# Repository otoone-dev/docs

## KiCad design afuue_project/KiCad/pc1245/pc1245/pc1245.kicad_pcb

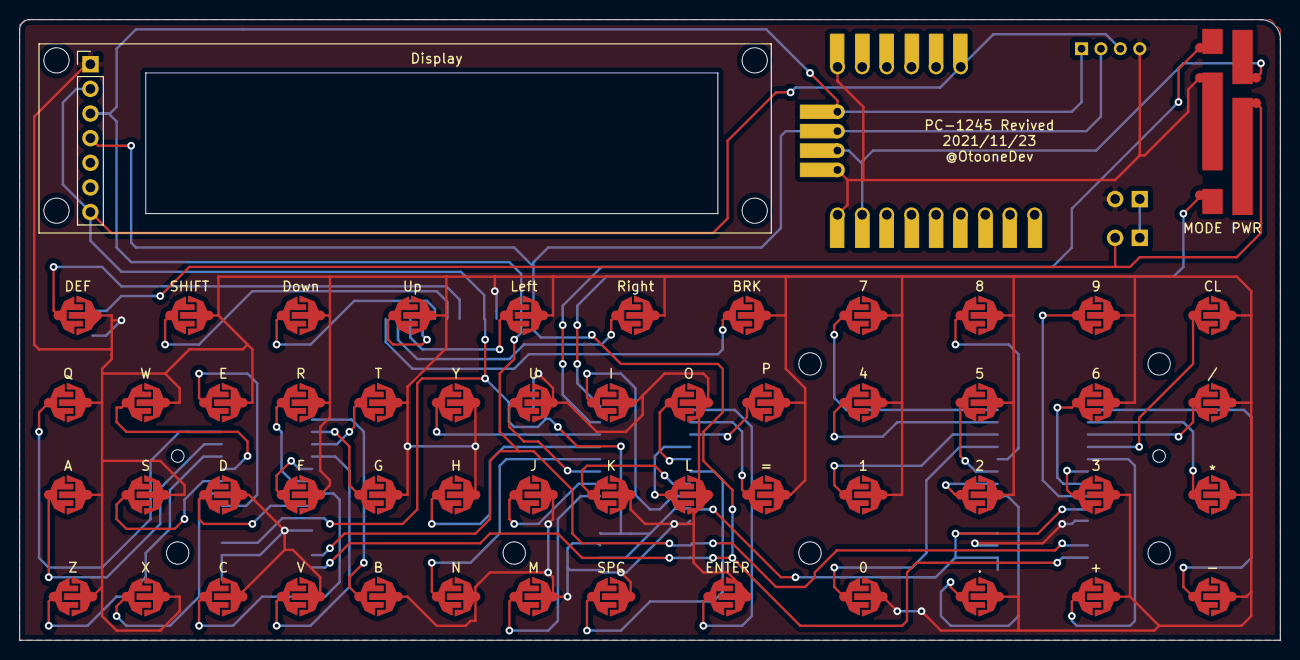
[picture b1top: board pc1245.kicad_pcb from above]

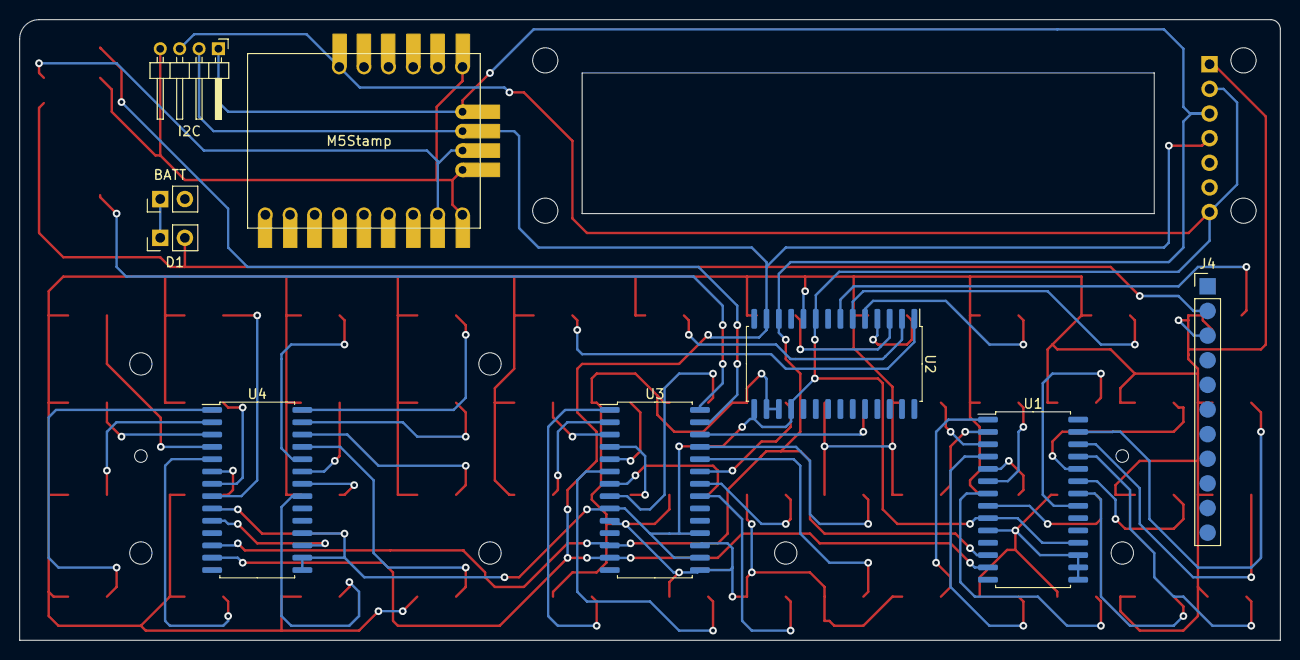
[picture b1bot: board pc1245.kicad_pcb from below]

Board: 2 copper layers, 130.0 x 64.0 mm, 64 parts (9 on the bottom side), 61 nets.

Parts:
0, 1, 2, 3, 4, 5, 6, 7, 8, 9, .: SW_Push; ContactPad_4mm
*: SW_Push; ContactPad_4mm
+: SW_Push; ContactPad_4mm
-: SW_Push; ContactPad_4mm
/: SW_Push; ContactPad_4mm
=: SW_Push; ContactPad_4mm
A: SW_Push; ContactPad_4mm
B: SW_Push; ContactPad_4mm
BATT: Conn_01x02; PinHeader_1x02_P2.54mm_Vertical
BRK: SW_Push; ContactPad_4mm
C: SW_Push; ContactPad_4mm
CL: SW_Push; ContactPad_4mm
D: SW_Push; ContactPad_4mm
D1: DIODE; PinHeader_1x02_P2.54mm_Vertical
DEF: SW_Push; ContactPad_4mm
Display: Conn_01x07; PinHeader_1x07_P2.54mm_Vertical
Down: SW_Push; ContactPad_4mm
E: SW_Push; ContactPad_4mm
ENTER: SW_Push; ContactPad_4mm
F: SW_Push; ContactPad_4mm
G: SW_Push; ContactPad_4mm
H: SW_Push; ContactPad_4mm
I: SW_Push; ContactPad_4mm
I2C: Conn_01x04; PinHeader_1x04_P2.00mm_Horizontal
J: SW_Push; ContactPad_4mm
J4: Conn_01x11; PinHeader_1x11_P2.54mm_Vertical
K: SW_Push; ContactPad_4mm
L: SW_Push; ContactPad_4mm
Left: SW_Push; ContactPad_4mm
M: SW_Push; ContactPad_4mm
M5Stamp: M5Stamp; M5StampPico
MODE: SW_SPDT; PC1245_ModeSlideSw
N: SW_Push; ContactPad_4mm
O: SW_Push; ContactPad_4mm
P: SW_Push; ContactPad_4mm
PWR: SW_SPST; PC1245_PowerSlideSw
Q: SW_Push; ContactPad_4mm
R: SW_Push; ContactPad_4mm
Right: SW_Push; ContactPad_4mm
S: SW_Push; ContactPad_4mm
SHIFT: SW_Push; ContactPad_4mm
SPC: SW_Push; ContactPad_4mm
T: SW_Push; ContactPad_4mm
U: SW_Push; ContactPad_4mm
U1, U2, U3, U4: MCP23017_SO; SOIC-28W_7.5x17.9mm_P1.27mm
Up: SW_Push; ContactPad_4mm
V: SW_Push; ContactPad_4mm
W: SW_Push; ContactPad_4mm
X: SW_Push; ContactPad_4mm
Y: SW_Push; ContactPad_4mm
Z: SW_Push; ContactPad_4mm

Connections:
+3V3: Display.2, Display.7, I2C.3, M5Stamp.19, U1.9, U1.18, U2.9, U2.15, U2.18, U3.9, U3.16, U3.18, U4.9, U4.15, U4.16, U4.18
+5V: M5Stamp.8, M5Stamp.11, PWR.1
-BATT: 0.2, 1.2, 2.2, 3.2, 4.2, 5.2, 6.2, 7.2, 8.2, 9.2, *.2, +.2, -.2, ..2, /.2, =.2, A.2, B.2, BATT.2, BRK.2, C.2, CL.2, D.2, DEF.2, Display.1, Down.2, E.2, ENTER.2, F.2, G.2, H.2, I.2, I2C.4, J.2, J4.3, K.2, L.2, Left.2, M.2, M5Stamp.9, M5Stamp.10, M5Stamp.14, MODE.2, N.2, O.2, P.2, Q.2, R.2, Right.2, S.2, SHIFT.2, SPC.2, T.2, U.2, U1.10, U1.15, U1.16, U1.17, U2.10, U2.16, U2.17, U3.10, U3.15, U3.17, U4.10, U4.17, Up.2, V.2, W.2, X.2, Y.2, Z.2
unnamed: BATT.1, D1.1
unnamed: D1.2, J4.2, PWR.2
unnamed: Display.3, I2C.1, M5Stamp.13, U1.12, U2.12, U3.12, U4.12
unnamed: Display.4, I2C.2, M5Stamp.12, U1.13, U2.13, U3.13, U4.13
unnamed: DEF.1, U2.7
unnamed: Q.1, U1.27
unnamed: A.1, U1.26
unnamed: U1.25, Z.1
unnamed: U1.24, W.1
unnamed: S.1, U1.23
unnamed: U1.22, X.1
unnamed: SHIFT.1, U2.6
unnamed: E.1, U1.21
unnamed: D.1, U1.8
unnamed: C.1, U1.7
unnamed: Down.1, U2.5
unnamed: R.1, U1.6
unnamed: F.1, U1.5
unnamed: U1.4, V.1
unnamed: T.1, U1.3
unnamed: G.1, U1.2
unnamed: B.1, U1.1
unnamed: U2.4, Up.1
unnamed: U3.26, Y.1
unnamed: H.1, U3.25
unnamed: N.1, U3.24
unnamed: Left.1, U2.3
unnamed: U.1, U3.23
unnamed: J.1, U3.22
unnamed: M.1, U3.21
unnamed: Right.1, U2.2
unnamed: I.1, U3.8
unnamed: K.1, U3.7
unnamed: SPC.1, U3.6
unnamed: O.1, U3.5
unnamed: L.1, U3.4
unnamed: ENTER.1, U3.1
unnamed: BRK.1, U2.1
unnamed: P.1, U3.3
unnamed: =.1, U3.2
unnamed: 7.1, U4.28
unnamed: 4.1, U4.27
unnamed: 1.1, U4.26
unnamed: 0.1, U4.25
unnamed: 8.1, U4.24
unnamed: 5.1, U4.23
unnamed: 2.1, U4.22
unnamed: ..1, U4.21
unnamed: 9.1, U4.8
unnamed: 6.1, U4.7
unnamed: 3.1, U4.6
unnamed: +.1, U4.5
unnamed: CL.1, U4.4
unnamed: /.1, U4.3
unnamed: *.1, U4.2
unnamed: -.1, U4.1
unnamed: MODE.1, U3.27
unnamed: MODE.3, U3.28

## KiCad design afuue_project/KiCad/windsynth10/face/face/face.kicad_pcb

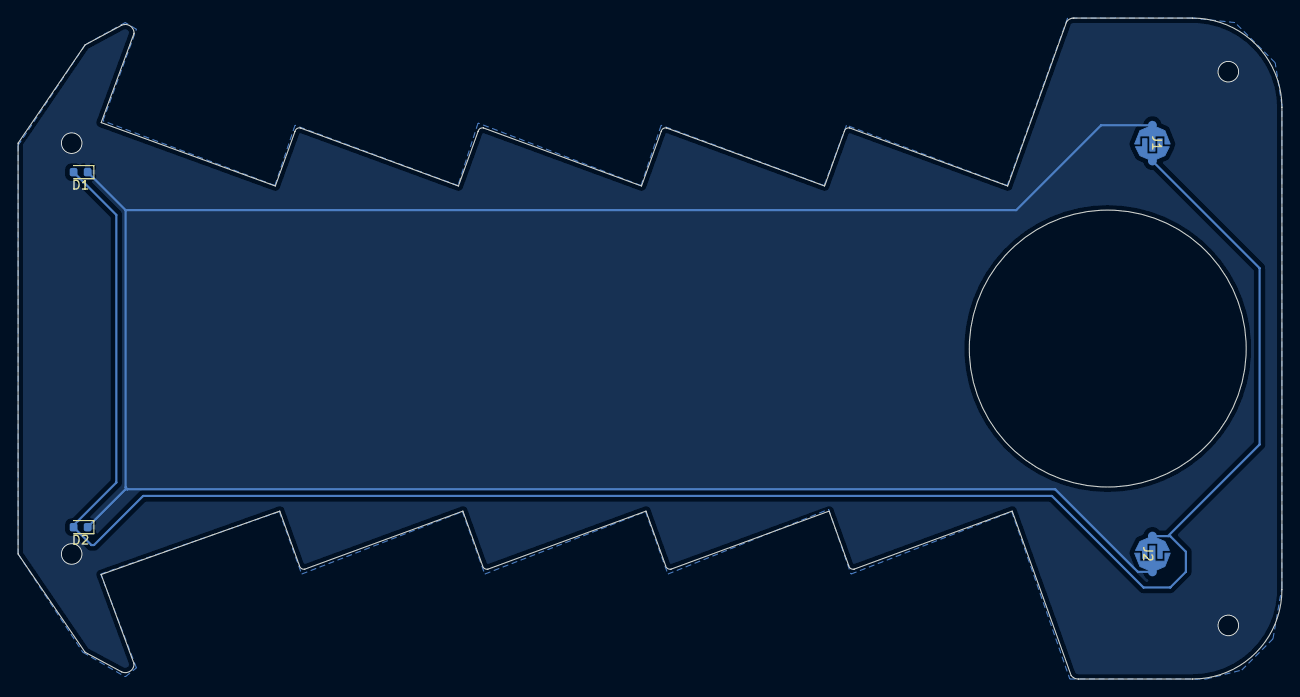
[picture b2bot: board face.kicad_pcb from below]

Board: 2 copper layers, 141.5 x 74.0 mm, 4 parts (4 on the bottom side), 2 nets.

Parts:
D1, D2: LED; LED_0603_1608Metric
J1, J2: Conn_01x02_Female; ContactPad_4mm

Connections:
GND: D1.1, D2.1, J1.2, J2.2
VCC: D1.2, D2.2, J1.1, J2.1

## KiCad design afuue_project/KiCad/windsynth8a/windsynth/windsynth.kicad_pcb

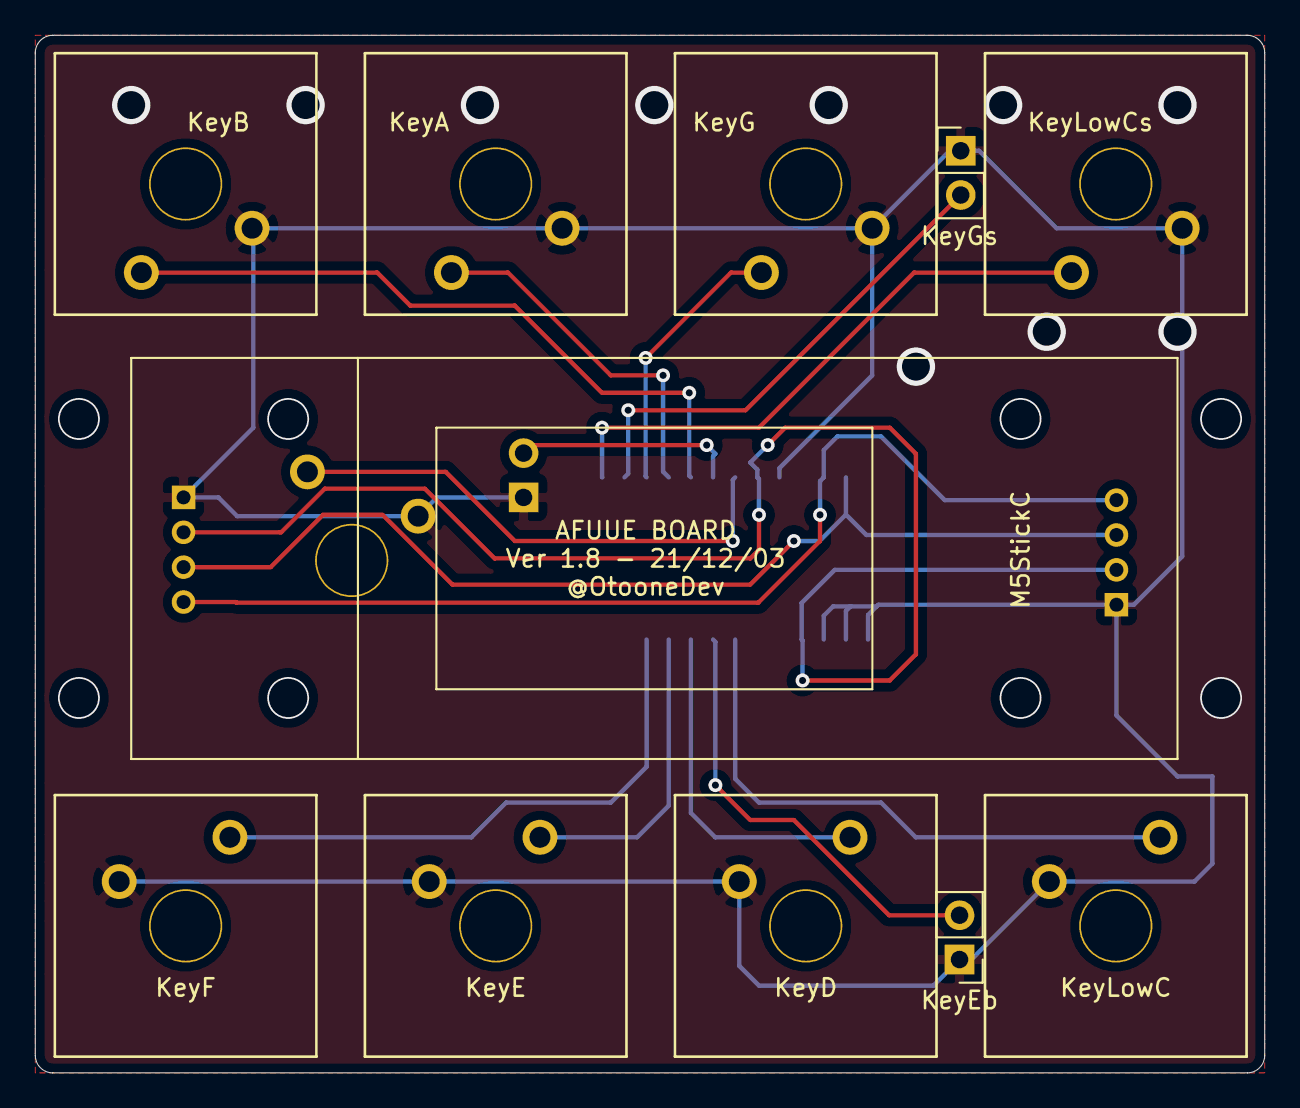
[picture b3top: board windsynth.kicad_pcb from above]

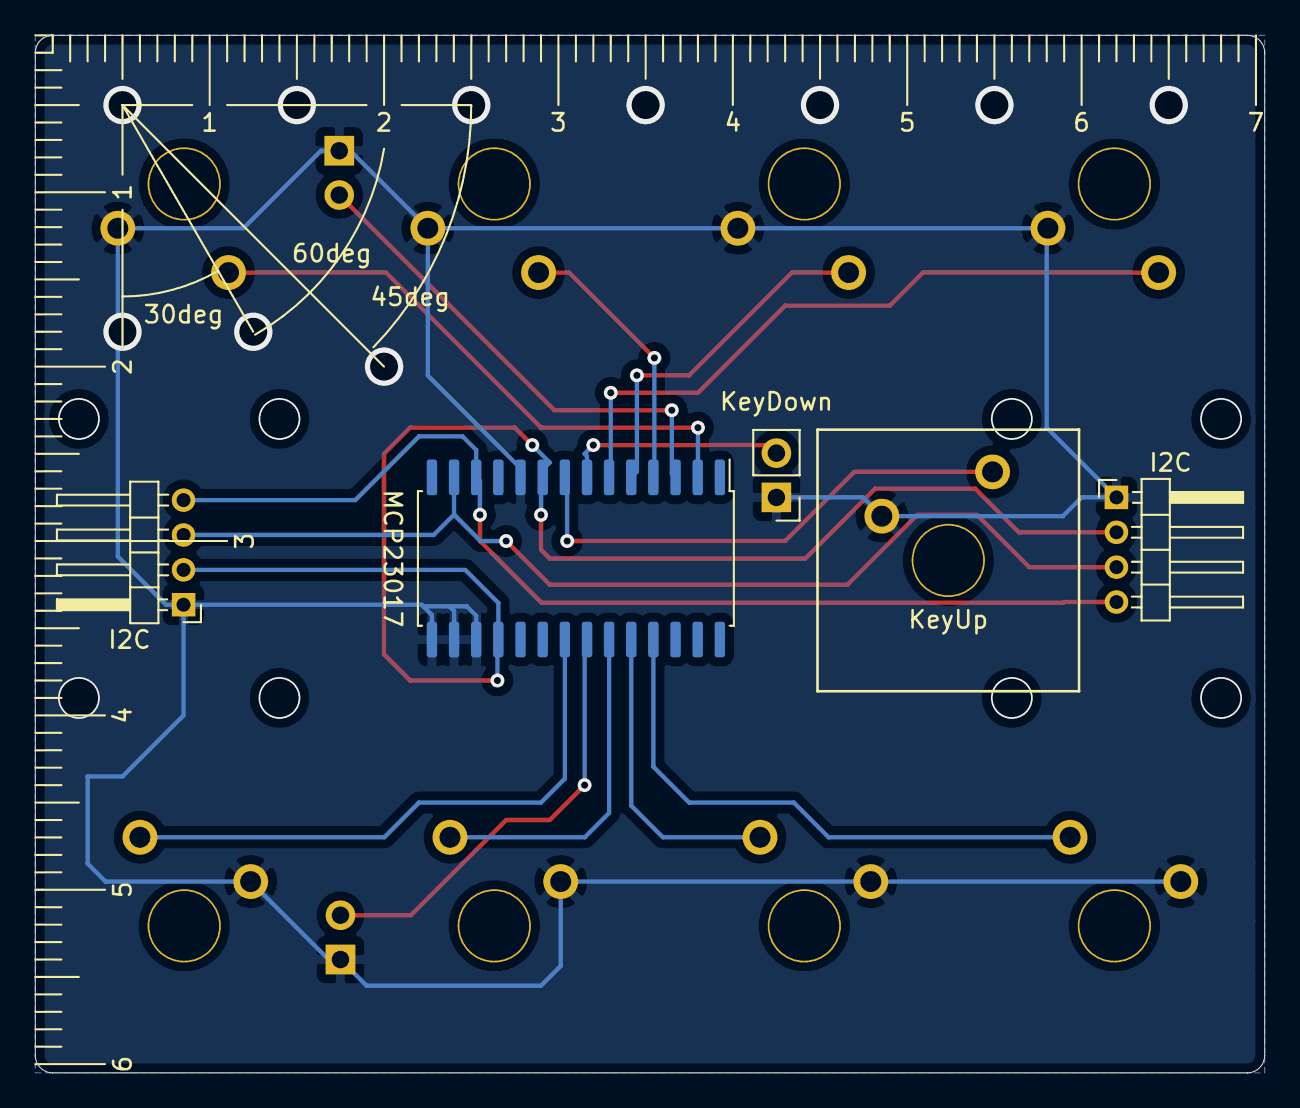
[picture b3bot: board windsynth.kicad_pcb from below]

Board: 2 copper layers, 70.5 x 59.5 mm, 15 parts (5 on the bottom side), 16 nets.

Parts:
I2C, I2C#2: Conn_01x04; PinHeader_1x04_P2.00mm_Horizontal
KeyA: SW_Push; CherryMX-Switch
KeyB: SW_Push; CherryMX-Switch
KeyD: SW_Push; CherryMX-Switch
KeyDown: SW_Push; PinHeader_1x02_P2.54mm_Vertical
KeyE: SW_Push; CherryMX-Switch
KeyEb: SW_Push; PinHeader_1x02_P2.54mm_Vertical
KeyF: SW_Push; CherryMX-Switch
KeyG: SW_Push; CherryMX-Switch
KeyGs: SW_Push; PinHeader_1x02_P2.54mm_Vertical
KeyLowC: SW_Push; CherryMX-Switch
KeyLowCs: SW_Push; CherryMX-Switch
KeyUp: SW_Push; CherryMX-Switch
MCP23017: MCP23S17_SP; SOIC-28W_7.5x17.9mm_P1.27mm

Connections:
+3V3: I2C.2, I2C#2.2, MCP23017.9, MCP23017.18
GND: I2C.1, I2C#2.1, KeyA.1, KeyB.1, KeyD.1, KeyDown.1, KeyE.1, KeyEb.1, KeyF.1, KeyG.1, KeyGs.1, KeyLowC.1, KeyLowCs.1, KeyUp.1, MCP23017.10, MCP23017.15, MCP23017.16, MCP23017.17
unnamed: I2C.3, I2C#2.3, MCP23017.13
unnamed: I2C.4, I2C#2.4, MCP23017.12
unnamed: KeyLowC.2, MCP23017.21
unnamed: KeyEb.2, MCP23017.22
unnamed: KeyD.2, MCP23017.23
unnamed: KeyE.2, MCP23017.24
unnamed: KeyF.2, MCP23017.25
unnamed: KeyLowCs.2, MCP23017.2
unnamed: KeyGs.2, MCP23017.3
unnamed: KeyG.2, MCP23017.4
unnamed: KeyA.2, MCP23017.5
unnamed: KeyB.2, MCP23017.6
unnamed: KeyDown.2, MCP23017.7
unnamed: KeyUp.2, MCP23017.8
